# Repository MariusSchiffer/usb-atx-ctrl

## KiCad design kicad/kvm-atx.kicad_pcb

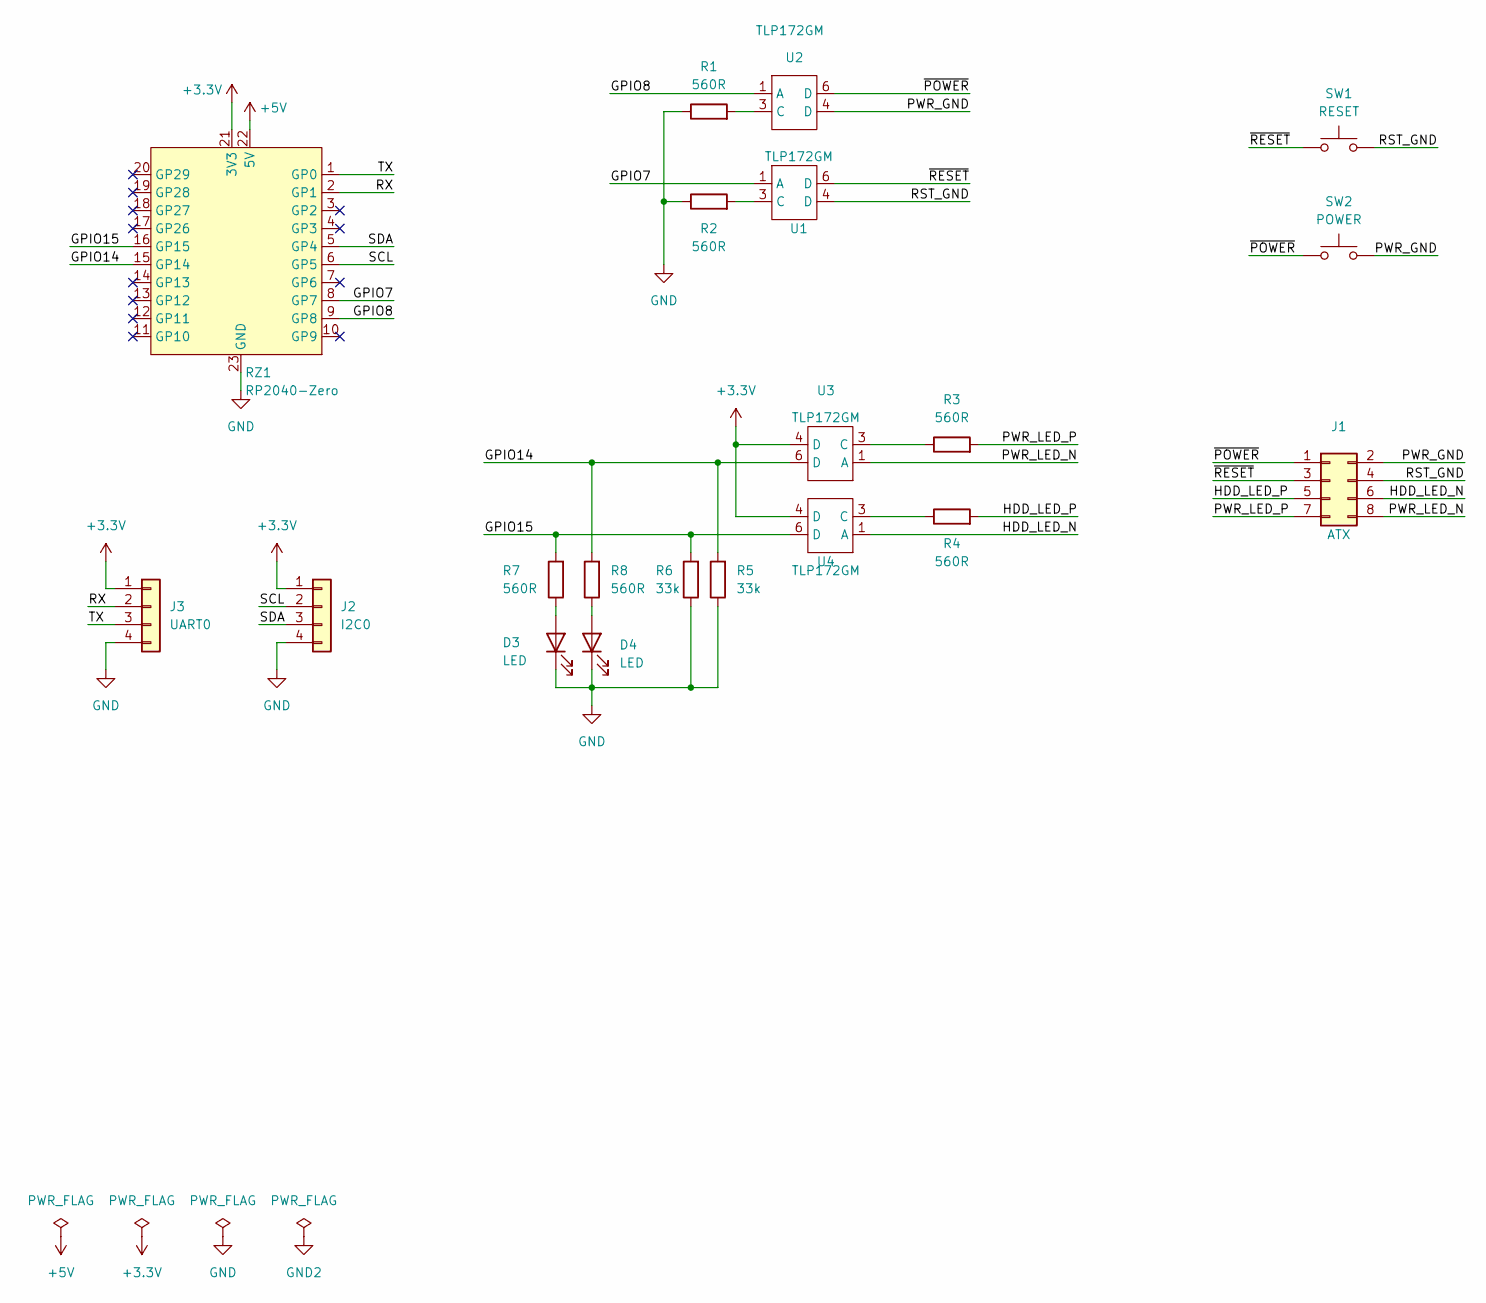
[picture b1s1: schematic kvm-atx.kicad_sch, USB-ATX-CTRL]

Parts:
D3, D4: LED; LED_0603_1608Metric
J1: ATX; IDC-Header_2x04_P2.54mm_Horizontal
J2: I2C0; PinHeader_1x04_P2.54mm_Vertical
J3: UART0; PinHeader_1x04_P2.54mm_Vertical
R1, R2, R3, R4, R7, R8: 560R; R_0603_1608Metric
R5, R6: 33k; R_0603_1608Metric
RZ1: RP2040-Zero
SW1: RESET; SW_PUSH_6mm
SW2: POWER; SW_PUSH_6mm
U1, U2, U3, U4: TLP172GM

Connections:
+3.3V: J2.1, J3.1, RZ1.21 (3V3), U3.4 (D), U4.4 (D)
+5V: RZ1.22 (5V)
/GPIO7: RZ1.8 (GP7), U1.1 (A)
/GPIO8: RZ1.9 (GP8), U2.1 (A)
/GPIO14: R5.2, R8.2, RZ1.15 (GP14), U3.6 (D)
/GPIO15: R6.2, R7.2, RZ1.16 (GP15), U4.6 (D)
/HDD_LED_N: J1.6, U4.1 (A)
/HDD_LED_P: J1.5, R4.2
/PWR_GND: J1.2, SW2.2, U2.4 (D)
/PWR_LED_N: J1.8, U3.1 (A)
/PWR_LED_P: J1.7, R3.2
/RST_GND: J1.4, SW1.2, U1.4 (D)
/RX: J3.2, RZ1.2 (GP1)
/SCL: J2.2, RZ1.6 (GP5)
/SDA: J2.3, RZ1.5 (GP4)
/TX: J3.3, RZ1.1 (GP0)
/~POWER: J1.1, SW2.1, U2.6 (D)
/~RESET: J1.3, SW1.1, U1.6 (D)
GND: D3.1 (K), D4.1 (K), J2.4, J3.4, R1.1, R2.1, R5.1, R6.1, RZ1.23 (GND)
unnamed: D3.2 (A), R7.1
unnamed: D4.2 (A), R8.1
unnamed: R2.2, U1.3 (C)
unnamed: R1.2, U2.3 (C)
unnamed: R3.1, U3.3 (C)
unnamed: R4.1, U4.3 (C)

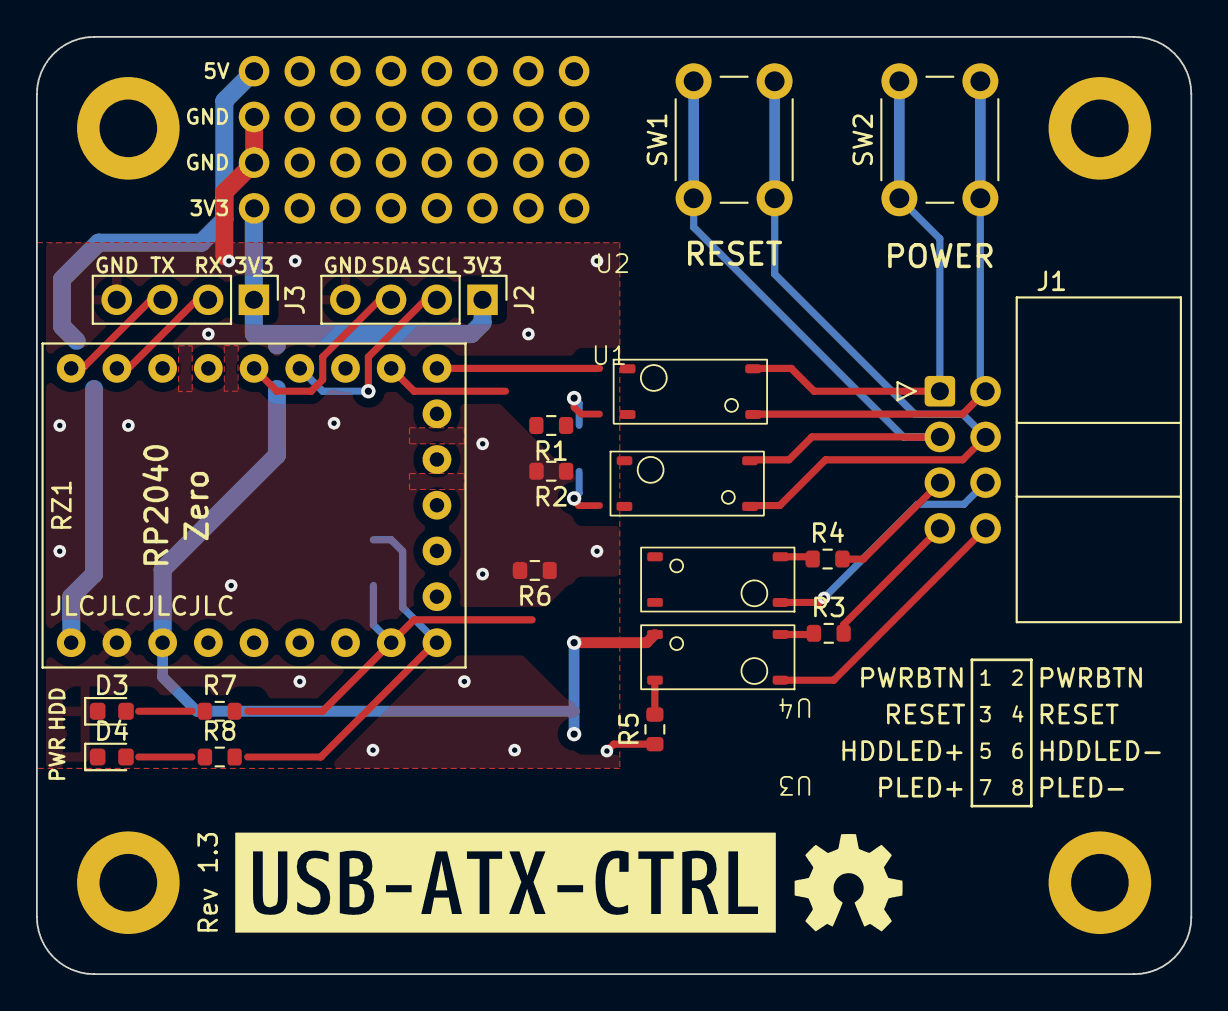
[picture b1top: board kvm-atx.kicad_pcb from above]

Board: 2 copper layers, 64.1 x 52.1 mm, 22 parts (0 on the bottom side), 24 nets.

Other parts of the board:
G1: LOGO
kibuzzard-639AEF10: G***; kibuzzard-639AEF10

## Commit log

2024-01-19 WIP assembly version
